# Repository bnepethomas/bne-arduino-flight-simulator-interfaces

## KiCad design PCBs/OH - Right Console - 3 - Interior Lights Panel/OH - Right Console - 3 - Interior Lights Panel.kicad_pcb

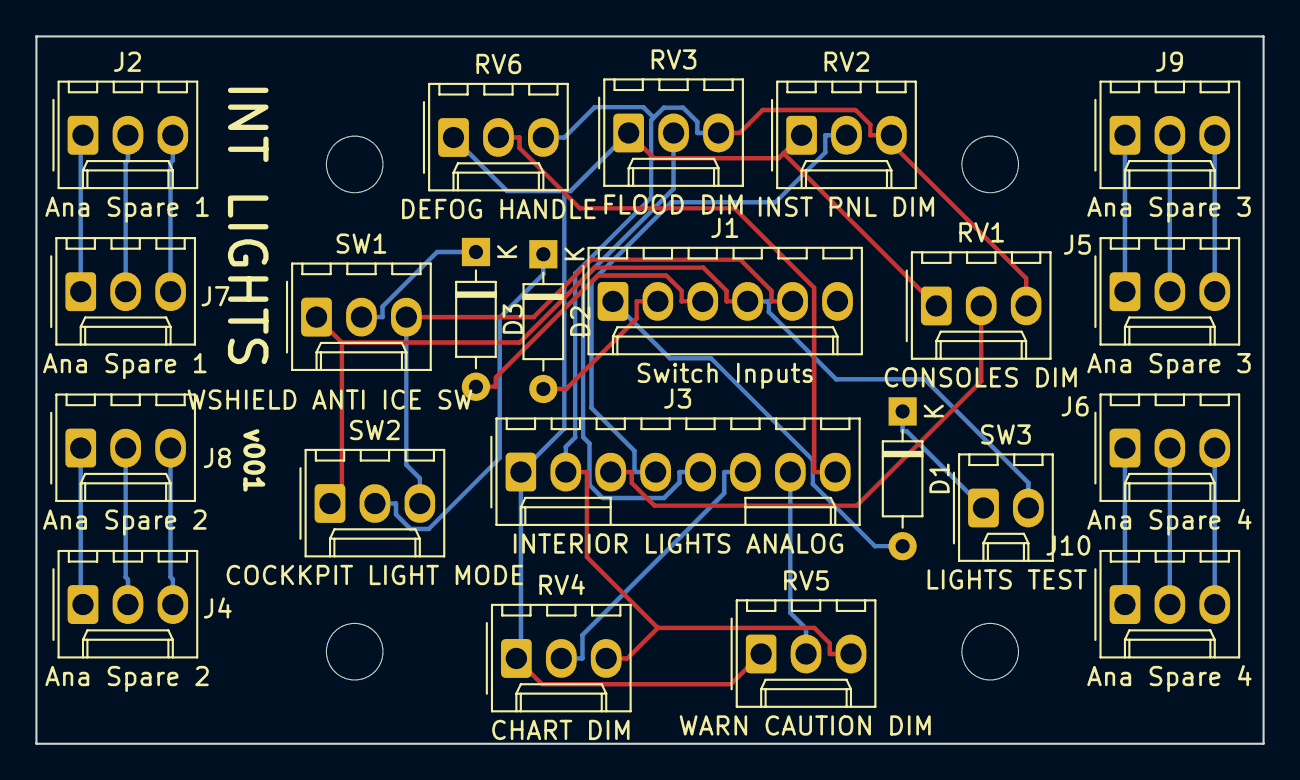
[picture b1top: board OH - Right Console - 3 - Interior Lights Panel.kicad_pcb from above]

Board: 2 copper layers, 69.4 x 40.0 mm, 26 parts (0 on the bottom side), 28 nets.

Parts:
D1, D2, D3: D; D_Signal_P7.62mm_Horizontal
H1, H2, H3, H4: MountingHole; MountingHole_3.2mm_M3
J1: Switch Inputs; Molex_1x06_P2.54mm_Vertical
J2, J7: Ana Spare 1; Molex_1x03_P2.54mm_Vertical
J3: INTERIOR LIGHTS ANALOG; Molex_1x08_P2.54mm_Vertical
J4, J8: Ana Spare 2; Molex_1x03_P2.54mm_Vertical
J5, J9: Ana Spare 3; Molex_1x03_P2.54mm_Vertical
J6, J10: Ana Spare 4; Molex_1x03_P2.54mm_Vertical
RV1: CONSOLES DIM; Molex_1x03_P2.54mm_Vertical
RV2: INST PNL DIM; Molex_1x03_P2.54mm_Vertical
RV3: FLOOD DIM; Molex_1x03_P2.54mm_Vertical
RV4: CHART DIM; Molex_1x03_P2.54mm_Vertical
RV5: WARN CAUTION DIM; Molex_1x03_P2.54mm_Vertical
RV6: DEFOG HANDLE; Molex_1x03_P2.54mm_Vertical
SW1: WSHIELD ANTI ICE SW; Molex_1x03_P2.54mm_Vertical
SW2: COCKKPIT LIGHT MODE; Molex_1x03_P2.54mm_Vertical
SW3: LIGHTS TEST; Molex_1x02_P2.54mm_Vertical

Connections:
/ANALOG+5V: J3.1, RV1.1, RV2.1, RV3.1, RV4.1, RV5.1, RV6.1
/ANALOG_GND: J3.2, RV1.3, RV2.3, RV3.3, RV4.3, RV5.3, RV6.3
/CHART: J3.6, RV4.2
/CONSOLES: J3.3, RV1.2
/Col1: D1.2, J1.1
/Col2: D2.2, J1.2
/Col3: D3.2, J1.3
/DEFOG: J3.8, RV6.2
/FLOOD: J3.5, RV3.2
/INST_PNL: J3.4, RV2.2
/ROW1: J1.4, SW1.1, SW2.1, SW3.2
/ROW2: J1.5, SW1.3, SW2.3
/WARN_CAUTION: J3.7, RV5.2
unnamed: D1.1, SW3.1
unnamed: D2.1, SW2.2
unnamed: D3.1, SW1.2
unnamed: J2.1, J7.1
unnamed: J2.2, J7.2
unnamed: J2.3, J7.3
unnamed: J4.1, J8.1
unnamed: J4.2, J8.2
unnamed: J4.3, J8.3
unnamed: J5.1, J9.1
unnamed: J5.2, J9.2
unnamed: J5.3, J9.3
unnamed: J6.1, J10.1
unnamed: J6.2, J10.2
unnamed: J6.3, J10.3

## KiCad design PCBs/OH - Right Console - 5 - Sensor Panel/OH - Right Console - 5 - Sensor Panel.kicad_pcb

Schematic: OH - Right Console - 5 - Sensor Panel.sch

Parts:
D1, D2, D3, D4, D5, D6: D; D_Signal_P7.62mm_Horizontal
D7: 1N4001; D_DO-41_SOD81_P10.16mm_Horizontal
H1, H2, H3, H4: MountingHole; MountingHole_3.2mm_M3
J1: Input Coulmns; Molex_1x03_P2.54mm_Vertical
J2: Laser Mag; Molex_1x02_P2.54mm_Vertical
J3: Input Rows; Molex_1x08_P2.54mm_Vertical
SOL1: Laser Mag; Molex_1x02_P2.54mm_Vertical
SW1: FLIR; Molex_1x03_P2.54mm_Vertical
SW2: LTD/R; Molex_1x02_P2.54mm_Vertical
SW3: LST/NFLR; Molex_1x02_P2.54mm_Vertical
SW4: RADAR PULL; Molex_1x02_P2.54mm_Vertical
SW5: RADAR; Molex_1x06_P2.54mm_Vertical
SW6: INS; Molex_1x10_P2.54mm_Vertical

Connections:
/Col2: D5.2 (A), J1.2
/Col3: D6.2 (A), J1.3
/Row1: J3.1, SW1.1, SW5.1, SW6.1
/Row2: J3.2, SW1.3, SW5.2, SW6.2
/Row3: J3.3, SW2.2 (B), SW5.3, SW6.3
/Row4: J3.4, SW3.2 (B), SW5.4, SW6.4
/Row5: J3.5, SW4.2, SW6.5
/Row6: J3.6, SW6.6
/Row7: J3.7, SW6.7
/Row8: J3.8, SW6.8
unnamed: D1.1 (K), SW1.2
unnamed: D1.2 (A), D2.2 (A), D3.2 (A), D4.2 (A), J1.1
unnamed: D2.1 (K), SW2.1 (A)
unnamed: D3.1 (K), SW3.1 (A)
unnamed: D4.1 (K), SW4.1
unnamed: D5.1 (K), SW5.6 (COM)
unnamed: D6.1 (K), SW6.10
unnamed: D7.1, J2.1, SOL1.1
unnamed: D7.2, J2.2, SOL1.2

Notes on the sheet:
-- 5. Sensor Panel define3PosTumb("FLIR_SW", 62, 3001, 439, "Sensor Panel", "FLIR Switch, ON/STBY/OFF") define3PosTumb("LTD_R_SW", 62, 3002, 441, "Sensor Panel", "LTD/R Switch, ---/SAFE/AFT") -- ARM position is handled by another parameter defineToggleSwitch("LST_NFLR_SW", 62, 3004, 442, "Sensor Pa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

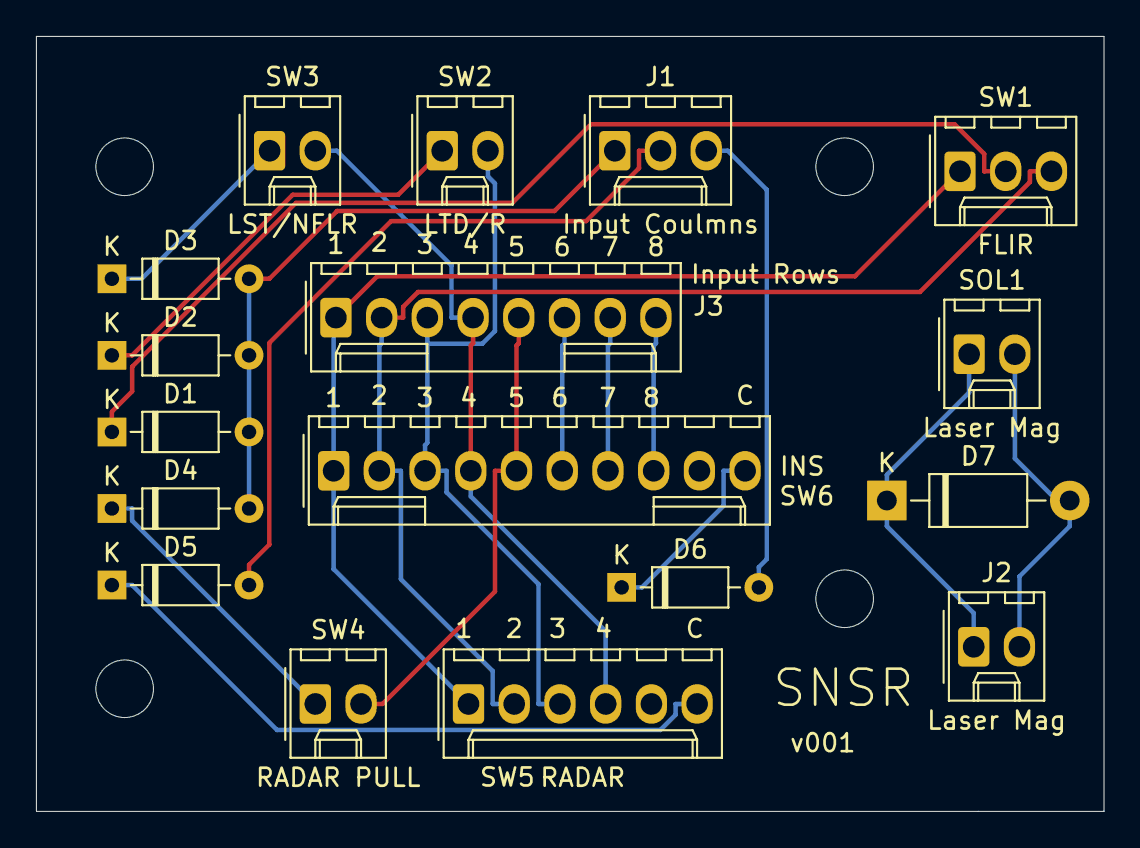
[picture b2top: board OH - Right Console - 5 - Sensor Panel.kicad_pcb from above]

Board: 2 copper layers, 59.3 x 43.1 mm, 21 parts (0 on the bottom side), 19 nets.

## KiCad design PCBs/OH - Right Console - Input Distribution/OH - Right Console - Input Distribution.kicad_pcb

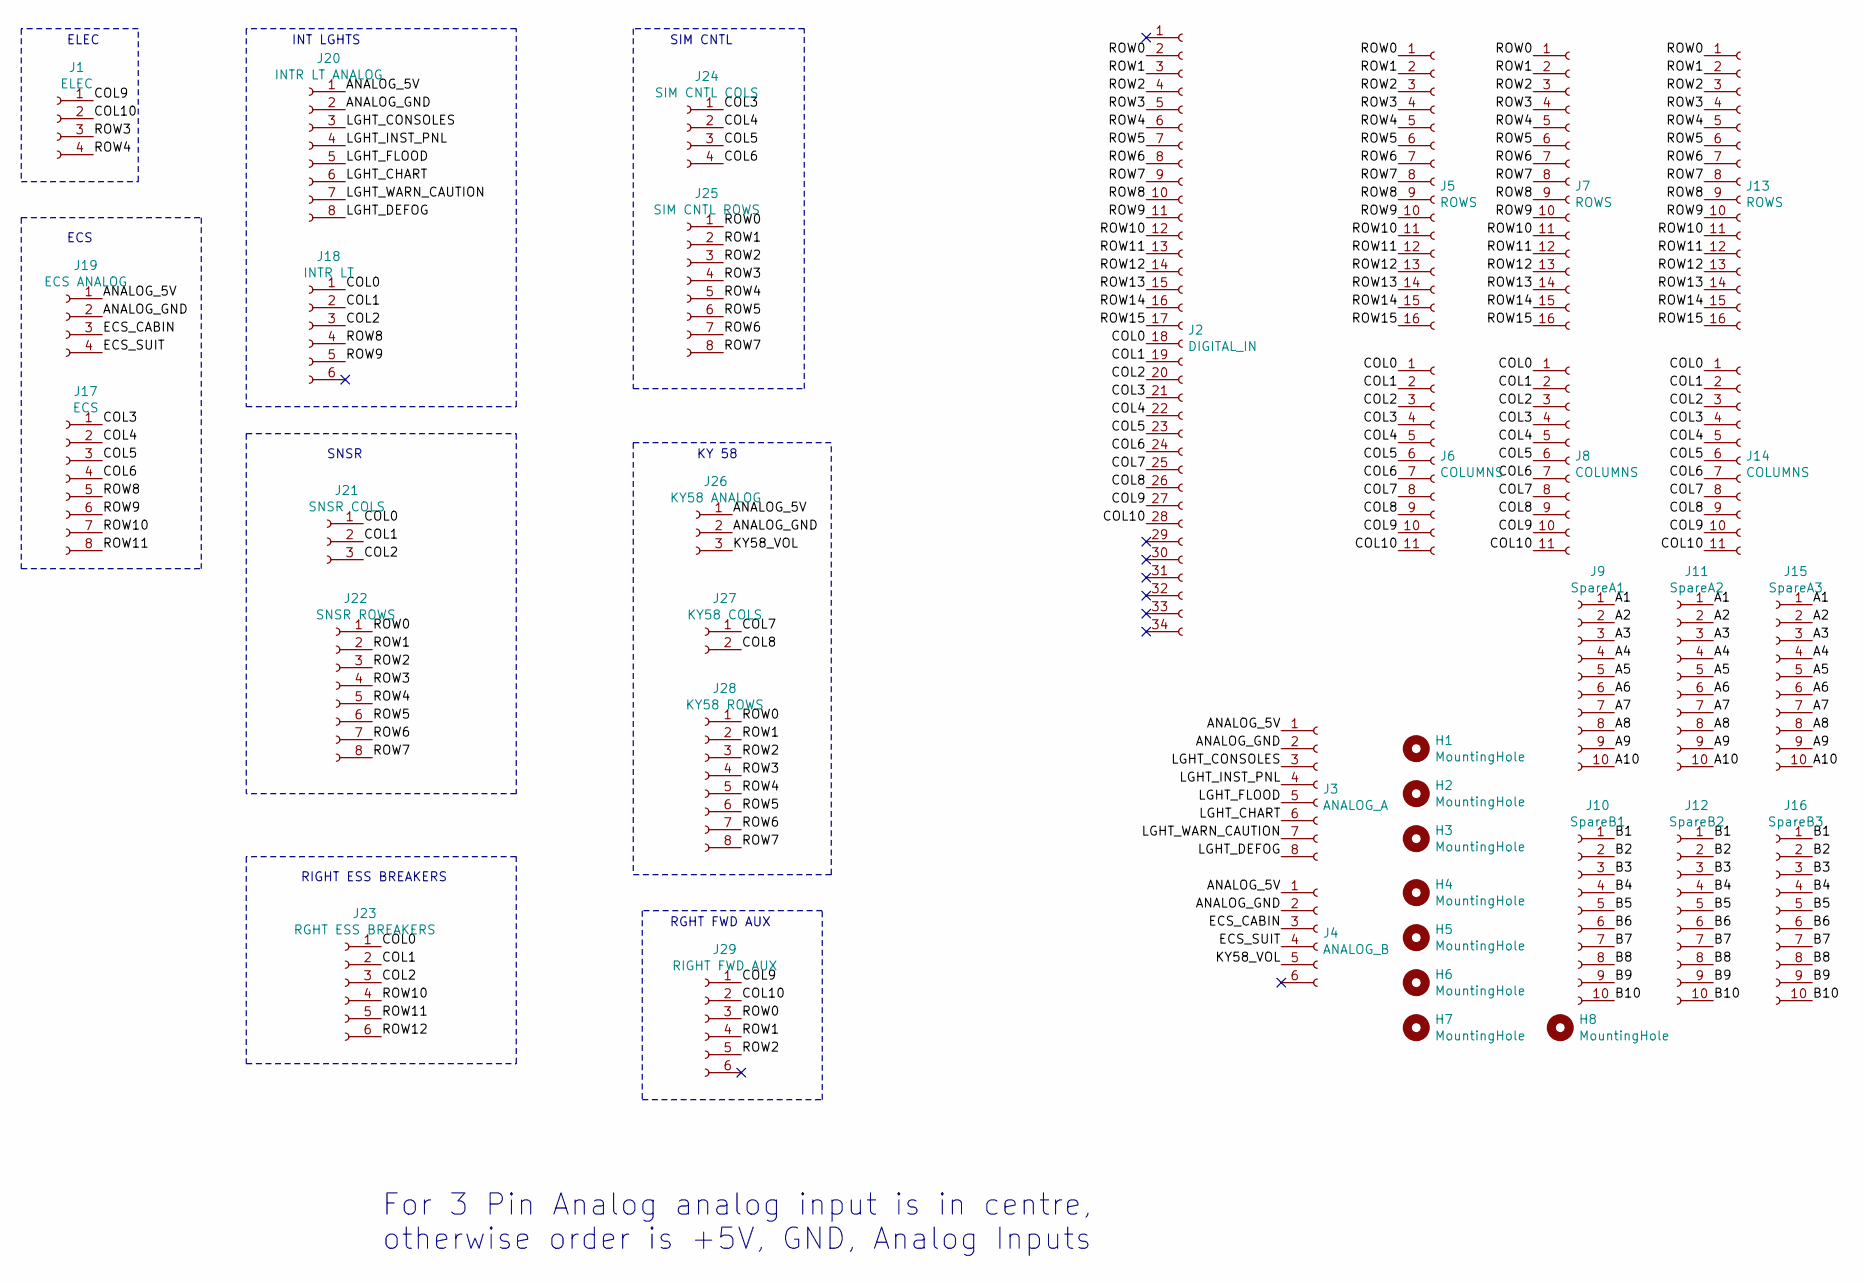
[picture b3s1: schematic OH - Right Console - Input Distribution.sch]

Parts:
H1, H2, H3, H4, H5, H6, H7, H8: MountingHole; MountingHole_3.2mm_M3
J1: ELEC; Molex_1x04_P2.54mm_Vertical
J2: DIGITAL_IN; IDC-Header_2x17_P2.54mm_Vertical
J3: ANALOG_A; Molex_1x08_P2.54mm_Vertical
J4: ANALOG_B; Molex_1x06_P2.54mm_Vertical
J5, J7, J13: ROWS; PinHeader_1x16_P2.54mm_Vertical
J6, J8, J14: COLUMNS; PinHeader_1x11_P2.54mm_Vertical
J9: SpareA1; Molex_1x10_P2.54mm_Vertical
J10: SpareB1; Molex_1x10_P2.54mm_Vertical
J11: SpareA2; Molex_1x10_P2.54mm_Vertical
J12: SpareB2; Molex_1x10_P2.54mm_Vertical
J15: SpareA3; Molex_1x10_P2.54mm_Vertical
J16: SpareB3; Molex_1x10_P2.54mm_Vertical
J17: ECS; Molex_1x08_P2.54mm_Vertical
J18: INTR LT; Molex_1x06_P2.54mm_Vertical
J19: ECS ANALOG; Molex_1x04_P2.54mm_Vertical
J20: INTR LT ANALOG; Molex_1x08_P2.54mm_Vertical
J21: SNSR COLS; Molex_1x03_P2.54mm_Vertical
J22: SNSR ROWS; Molex_1x08_P2.54mm_Vertical
J23: RGHT ESS BREAKERS; Molex_1x06_P2.54mm_Vertical
J24: SIM CNTL COLS; Molex_1x04_P2.54mm_Vertical
J25: SIM CNTL ROWS; Molex_1x08_P2.54mm_Vertical
J26: KY58 ANALOG; Molex_1x03_P2.54mm_Vertical
J27: KY58 COLS; Molex_1x02_P2.54mm_Vertical
J28: KY58 ROWS; Molex_1x08_P2.54mm_Vertical
J29: RIGHT FWD AUX; Molex_1x06_P2.54mm_Vertical

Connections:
/A1: J9.1, J11.1, J15.1
/A2: J9.2, J11.2, J15.2
/A3: J9.3, J11.3, J15.3
/A4: J9.4, J11.4, J15.4
/A5: J9.5, J11.5, J15.5
/A6: J9.6, J11.6, J15.6
/A7: J9.7, J11.7, J15.7
/A8: J9.8, J11.8, J15.8
/A9: J9.9, J11.9, J15.9
/A10: J9.10, J11.10, J15.10
/ANALOG_5V: J3.1, J4.1, J19.1, J20.1, J26.1
/ANALOG_GND: J3.2, J4.2, J19.2, J20.2, J26.2
/B1: J10.1, J12.1, J16.1
/B2: J10.2, J12.2, J16.2
/B3: J10.3, J12.3, J16.3
/B4: J10.4, J12.4, J16.4
/B5: J10.5, J12.5, J16.5
/B6: J10.6, J12.6, J16.6
/B7: J10.7, J12.7, J16.7
/B8: J10.8, J12.8, J16.8
/B9: J10.9, J12.9, J16.9
/B10: J10.10, J12.10, J16.10
/COL0: J2.18, J6.1, J8.1, J14.1, J18.1, J21.1, J23.1
/COL1: J2.19, J6.2, J8.2, J14.2, J18.2, J21.2, J23.2
/COL2: J2.20, J6.3, J8.3, J14.3, J18.3, J21.3, J23.3
/COL3: J2.21, J6.4, J8.4, J14.4, J17.1, J24.1
/COL4: J2.22, J6.5, J8.5, J14.5, J17.2, J24.2
/COL5: J2.23, J6.6, J8.6, J14.6, J17.3, J24.3
/COL6: J2.24, J6.7, J8.7, J14.7, J17.4, J24.4
/COL7: J2.25, J6.8, J8.8, J14.8, J27.1
/COL8: J2.26, J6.9, J8.9, J14.9, J27.2
/COL9: J1.1, J2.27, J6.10, J8.10, J14.10, J29.1
/COL10: J1.2, J2.28, J6.11, J8.11, J14.11, J29.2
/ECS_CABIN: J4.3, J19.3
/ECS_SUIT: J4.4, J19.4
/KY58_VOL: J4.5, J26.3
/LGHT_CHART: J3.6, J20.6
/LGHT_CONSOLES: J3.3, J20.3
/LGHT_DEFOG: J3.8, J20.8
/LGHT_FLOOD: J3.5, J20.5
/LGHT_INST_PNL: J3.4, J20.4
/LGHT_WARN_CAUTION: J3.7, J20.7
/ROW0: J2.2, J5.1, J7.1, J13.1, J22.1, J25.1, J28.1, J29.3
/ROW1: J2.3, J5.2, J7.2, J13.2, J22.2, J25.2, J28.2, J29.4
/ROW2: J2.4, J5.3, J7.3, J13.3, J22.3, J25.3, J28.3, J29.5
/ROW3: J1.3, J2.5, J5.4, J7.4, J13.4, J22.4, J25.4, J28.4
/ROW4: J1.4, J2.6, J5.5, J7.5, J13.5, J22.5, J25.5, J28.5
/ROW5: J2.7, J5.6, J7.6, J13.6, J22.6, J25.6, J28.6
/ROW6: J2.8, J5.7, J7.7, J13.7, J22.7, J25.7, J28.7
/ROW7: J2.9, J5.8, J7.8, J13.8, J22.8, J25.8, J28.8
/ROW8: J2.10, J5.9, J7.9, J13.9, J17.5, J18.4
/ROW9: J2.11, J5.10, J7.10, J13.10, J17.6, J18.5
/ROW10: J2.12, J5.11, J7.11, J13.11, J17.7, J23.4
/ROW11: J2.13, J5.12, J7.12, J13.12, J17.8, J23.5
/ROW12: J2.14, J5.13, J7.13, J13.13, J23.6
/ROW13: J2.15, J5.14, J7.14, J13.14
/ROW14: J2.16, J5.15, J7.15, J13.15
/ROW15: J2.17, J5.16, J7.16, J13.16

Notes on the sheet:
ELEC
For 3 Pin Analog analog input is in centre, otherwise order is +5V, GND, Analog Inputs
ECS
INT LGHTS
SNSR
RIGHT ESS BREAKERS
SIM CNTL
KY 58
RGHT FWD AUX

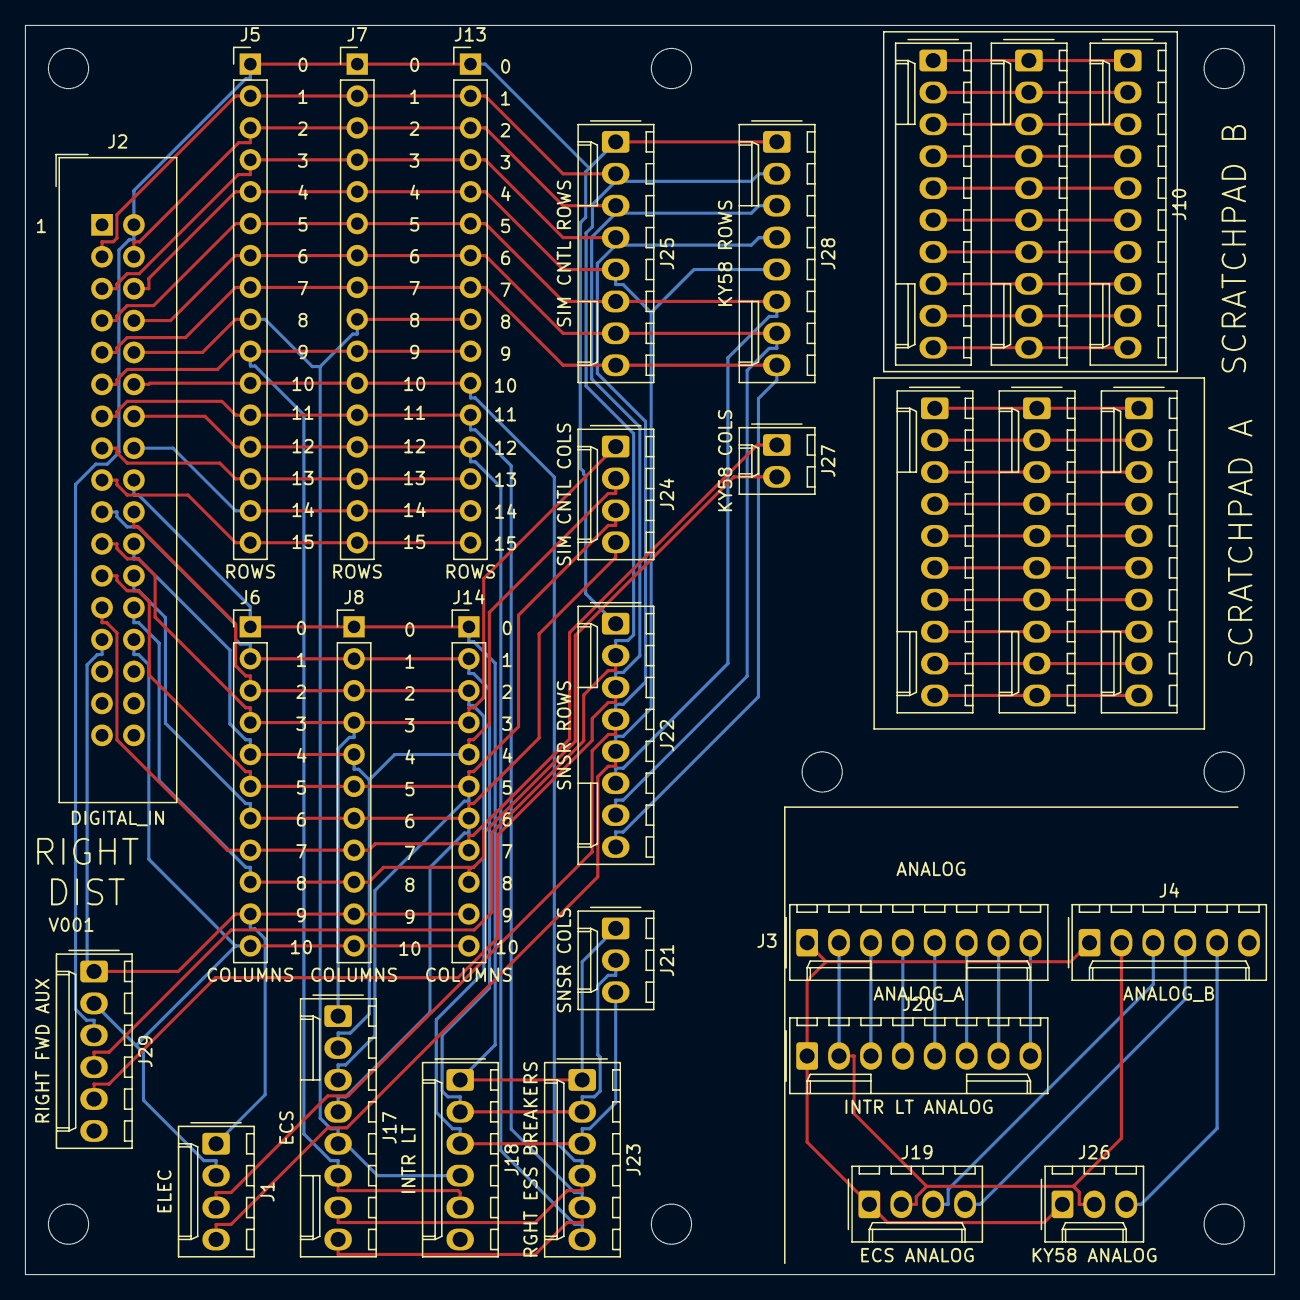
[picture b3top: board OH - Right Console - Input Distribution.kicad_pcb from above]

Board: 2 copper layers, 99.4 x 99.4 mm, 37 parts (0 on the bottom side), 58 nets.

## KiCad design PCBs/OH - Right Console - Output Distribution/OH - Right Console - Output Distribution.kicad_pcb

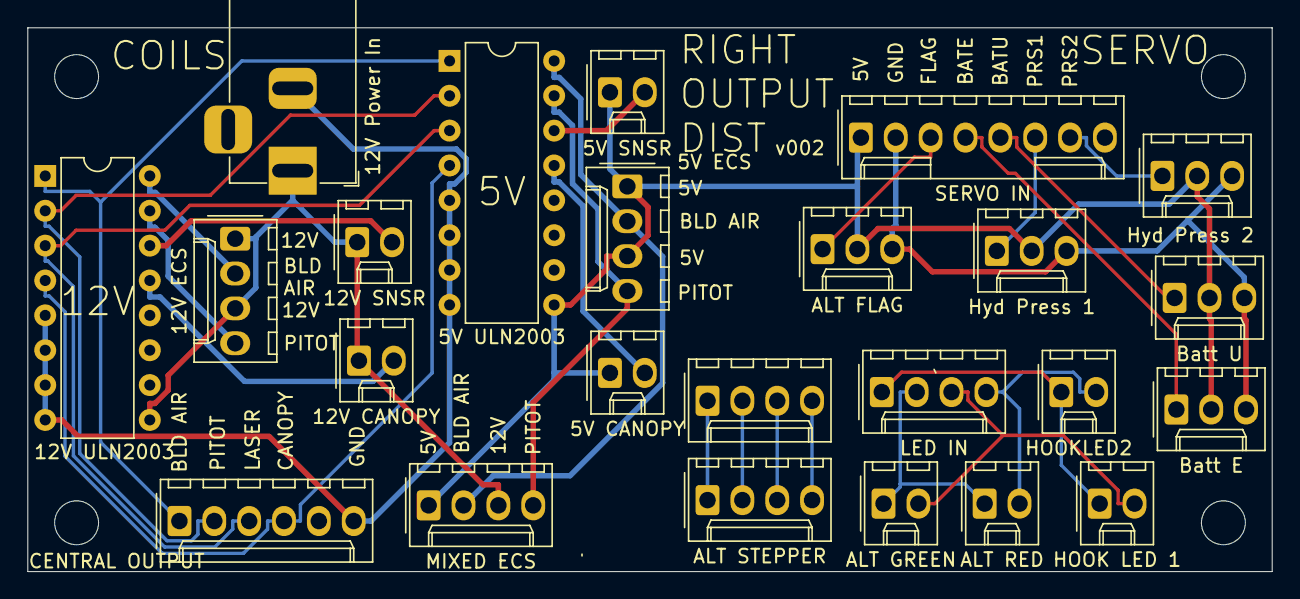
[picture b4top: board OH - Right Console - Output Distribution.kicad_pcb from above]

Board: 2 copper layers, 90.7 x 39.6 mm, 28 parts (0 on the bottom side), 29 nets.

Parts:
H1, H2, H3, H4: MountingHole; MountingHole_3.2mm_M3
J1: CENTRAL OUTPUT; Molex_1x06_P2.54mm_Vertical
J2: SERVO IN; Molex_1x08_P2.54mm_Vertical
J3: 12V Power In; BarrelJack_Horizontal
J4, J7: ALT STEPPER; Molex_1x04_P2.54mm_Vertical
J5: 5V ECS; Molex_1x04_P2.54mm_Vertical
J6: LED IN; Molex_1x04_P2.54mm_Vertical
J8: ALT FLAG; Molex_1x03_P2.54mm_Vertical
J9: HOOK LED 1; Molex_1x02_P2.54mm_Vertical
J10: ALT GREEN; Molex_1x02_P2.54mm_Vertical
J11: HOOKLED2; Molex_1x02_P2.54mm_Vertical
J12: ALT RED; Molex_1x02_P2.54mm_Vertical
J13: 12V ECS; Molex_1x04_P2.54mm_Vertical
J14: 12V SNSR; Molex_1x02_P2.54mm_Vertical
J15: 12V CANOPY; Molex_1x02_P2.54mm_Vertical
J16: Batt U; Molex_1x03_P2.54mm_Vertical
J17: Batt E; Molex_1x03_P2.54mm_Vertical
J18: Hyd Press 1; Molex_1x03_P2.54mm_Vertical
J19: Hyd Press 2; Molex_1x03_P2.54mm_Vertical
J20: 5V SNSR; Molex_1x02_P2.54mm_Vertical
J21: 5V CANOPY; Molex_1x02_P2.54mm_Vertical
J22: MIXED ECS; Molex_1x04_P2.54mm_Vertical
U1: 12V ULN2003; DIP-16_W7.62mm
U2: 5V ULN2003; DIP-16_W7.62mm

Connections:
/5V_Out_Bleed_Air_Sol: J5.2, J22.2, U2.16
/5V_Out_Canopy_Mag: J21.2, U2.13
/5V_Out_Laser_Arm_Mag: J20.2, U2.14
/5V_Out_Pitot_Heat_Mag: J5.4, J22.4, U2.15
/12V_Out_Bleed_Air_Sol: J13.2, U1.16
/12V_Out_Canopy_Mag: J15.2, U1.13
/12V_Out_Laser_Arm_Mag: J14.2, U1.14
/12V_Out_Pitot_Heat_Mag: J13.4, U1.15
/+12V: J3.1, J13.1, J13.3, J14.1, J15.1, J22.3, U1.9
/ALT_FLAG_PWM: J2.3, J8.1
/ALT_STEPPER_1A: J4.1, J7.1
/ALT_STEPPER_1B: J4.2, J7.2
/ALT_STEPPER_2A: J4.3, J7.3
/ALT_STEPPER_2B: J4.4, J7.4
/BATT_E_PWM: J2.4, J17.1
/BATT_U_PWM: J2.5, J16.1
/GND: J1.6, J3.2, U1.5, U1.6, U1.7, U1.8, U2.5, U2.6, U2.7, U2.8
/HYD_PRESS_1_PWM: J2.6, J18.1
/HYD_PRESS_2_PWM: J2.7, J19.1
/In_Bleed_Air_Sol: J1.1, U1.1, U2.1
/In_Canopy_Mag: J1.4, U1.4, U2.4
/In_Laser_Arm_Mag: J1.3, U1.3, U2.3
/In_Pitot_Heat_Mag: J1.2, U1.2, U2.2
/LEDCOL1: J6.3, J9.2, J10.2
/LEDCOL2: J6.4, J11.2, J12.2
/LEDROW1: J6.1, J9.1, J11.1
/LEDROW2: J6.2, J10.1, J12.1
/SERVO_5V: J2.1, J5.1, J5.3, J8.2, J16.2, J17.2, J18.2, J19.2, J20.1, J21.1, J22.1, U2.9
/SERVO_GND: J2.2, J8.3, J16.3, J17.3, J18.3, J19.3

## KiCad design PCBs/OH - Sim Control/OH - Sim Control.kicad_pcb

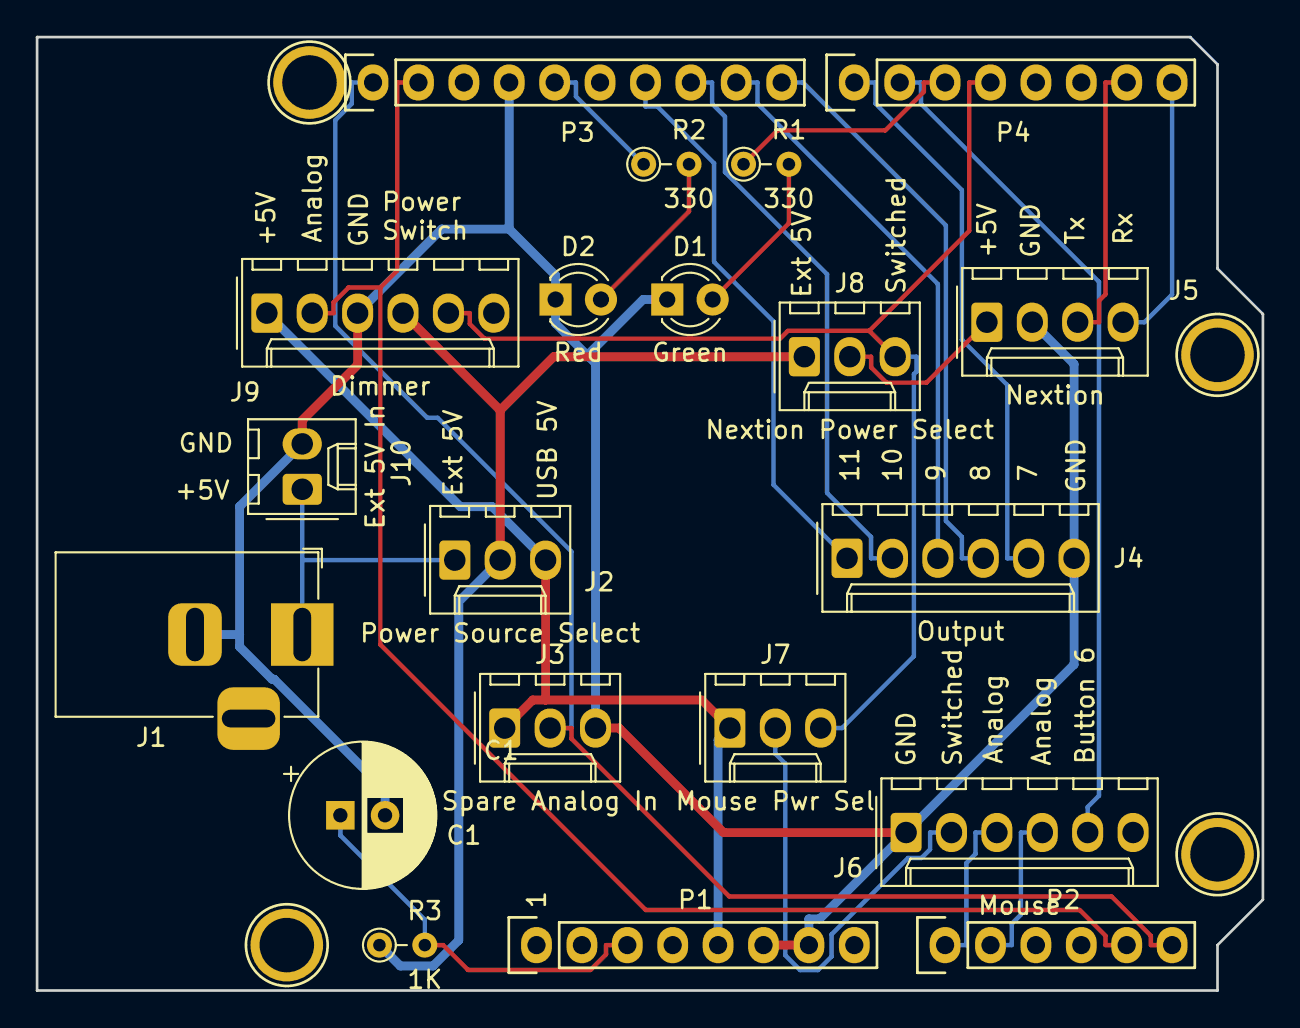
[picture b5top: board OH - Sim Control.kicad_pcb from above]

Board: 2 copper layers, 68.6 x 53.3 mm, 24 parts (0 on the bottom side), 24 nets.

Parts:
C1: CP; PT_CP_Radial_D8.0mm_P2.50mm
D1: Green; LED_D3.0mm
D2: Red; LED_D3.0mm
J1: Ext 5V In; BarrelJack_Horizontal
J2: Power Source Select; Molex_1x03_P2.54mm_Vertical
J3: Spare Analog In; Molex_1x03_P2.54mm_Vertical
J4: Output; Molex_1x06_P2.54mm_Vertical
J5: Nextion; Molex_1x04_P2.54mm_Vertical
J6: Mouse; Molex_1x06_P2.54mm_Vertical
J7: Mouse Pwr Sel; Molex_1x03_P2.54mm_Vertical
J8: Nextion Power Select; Molex_1x03_P2.54mm_Vertical
J9: Dimmer; Molex_1x06_P2.54mm_Vertical
J10: Ext 5V In; Molex_1x02_P2.54mm_Vertical
P1: Power; Socket_Strip_Arduino_1x08
P2: Analog; Socket_Strip_Arduino_1x06
P3: Digital; Socket_Strip_Arduino_1x10
P4: Digital; Socket_Strip_Arduino_1x08
P5, P6, P7, P8: CONN_01X01; Arduino_1pin
R1, R2: 330; PT_R_Axial_DIN0204_L3.6mm_D1.6mm_P2.54mm_Vertical
R3: 1K; PT_R_Axial_DIN0204_L3.6mm_D1.6mm_P2.54mm_Vertical

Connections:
+5V: J2.3, J3.1, J7.1, J9.1, P1.5
+5VD: J2.2, J8.1, J9.4, R3.1
/0(Rx): J5.4, P4.8
/1(Tx): J5.3, P4.7
/5(**): P4.3, R1.1
/6: J6.5, P4.2
/7: J4.5, P4.1
/8: J4.4, P3.10
/9: J4.3, P3.9
/10: J4.2, P3.8
/11: J4.1, P3.7
/13(SCK): P3.5, R2.1
/A0: J6.3, P2.1
/A1: J6.4, P2.2
/A4(SDA): J9.2, P2.5, P3.2
/A5(SCL): J3.2, P2.6, P3.1
/Reset: C1.1, P1.3, R3.2
/Swtiched_5VD: J7.3, J8.3, J9.5, P4.4
GND: C1.2, D1.1, D2.1, J1.2, J3.3, J4.6, J5.2, J6.1, J9.3, J10.2, P1.6, P1.7, P3.4
unnamed: D1.2, R1.2
unnamed: D2.2, R2.2
unnamed: J1.1, J2.1, J10.1
unnamed: J5.1, J8.2
unnamed: J6.2, J7.2

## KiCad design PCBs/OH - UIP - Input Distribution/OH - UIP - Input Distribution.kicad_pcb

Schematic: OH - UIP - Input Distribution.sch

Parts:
D1, D2, D3, D4: D; D_Signal_P7.62mm_Horizontal
H1, H2, H3, H4, H5, H6, H7, H8: MountingHole; MountingHole_3.2mm_M3
J1: JET STATION SEL; Molex_1x06_P2.54mm_Vertical
J2: AP COL; Molex_1x03_P2.54mm_Vertical
J3: LEFT DDI COL; Molex_1x06_P2.54mm_Vertical
J4: LEFT DDI ROW; Molex_1x06_P2.54mm_Vertical
J5: RIGHT DDI COL; Molex_1x06_P2.54mm_Vertical
J6: RIGHT DDI ROW; Molex_1x06_P2.54mm_Vertical
J7: UFC COL; Molex_1x04_P2.54mm_Vertical
J8: UFC ROW; Molex_1x06_P2.54mm_Vertical
J9: AMPCD COL; Molex_1x04_P2.54mm_Vertical
J10: AMPCD ROW; Molex_1x08_P2.54mm_Vertical
J11: RWR CONTROL; Molex_1x08_P2.54mm_Vertical
J12: IFEI; Molex_1x08_P2.54mm_Vertical
J13: BIT; Molex_1x02_P2.54mm_Vertical
J14: MASTER ARM; Molex_1x06_P2.54mm_Vertical
J15: HUD CONTROL; Molex_1x06_P2.54mm_Vertical
J16: ECM; Molex_1x08_P2.54mm_Vertical
J17: SPIN; Molex_1x04_P2.54mm_Vertical
J18: LEFT EWI COL; Molex_1x02_P2.54mm_Vertical
J19: LEFT EWI ROW; Molex_1x02_P2.54mm_Vertical
J20: REWICOL; Molex_1x02_P2.54mm_Vertical
J21: REWIROW; Molex_1x02_P2.54mm_Vertical
J22: IFEI BRIGHTNESS; Molex_1x03_P2.54mm_Vertical
J23: SPIN ANALOG; Molex_1x03_P2.54mm_Vertical
J24: STANDBY ANALOG; Molex_1x03_P2.54mm_Vertical
J25: LEFT DDI ANALOG; Molex_1x04_P2.54mm_Vertical
J26: AMPCD-HDG; Molex_1x03_P2.54mm_Vertical
J27: ENCODERS; Molex_1x10_P2.54mm_Vertical
J28: HUD ANALOG; Molex_1x06_P2.54mm_Vertical
J29: RWR ANALOG; Molex_1x04_P2.54mm_Vertical
J30: RIGHT DDI ANALOG; Molex_1x04_P2.54mm_Vertical
J31: ANALOG B; Molex_1x10_P2.54mm_Vertical
J32: ANALOG A; Molex_1x08_P2.54mm_Vertical
J33: AMPCD-CRS; Molex_1x03_P2.54mm_Vertical
J34: STANDBY ENCODERS; Molex_1x06_P2.54mm_Vertical
J35: UFC LEFT ENCODER; Molex_1x06_P2.54mm_Vertical
J36: UFC RIGHT ENCODER; Molex_1x06_P2.54mm_Vertical
J37: AMPCD-BRIGHT; Molex_1x03_P2.54mm_Vertical
J38: DIGITAL_IN; IDC-Header_2x17_P2.54mm_Vertical
J39: ROWS; PinHeader_1x16_P2.54mm_Vertical
J40: COLUMNS; PinHeader_1x11_P2.54mm_Vertical
J41: AP ROW; Molex_1x03_P2.54mm_Vertical

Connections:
/AMPCD-BRIGHTNESS: J31.10, J37.2
/ANALOG_5V: J22.1, J23.1, J24.1, J25.1, J28.1, J29.1, J30.1, J31.1, J32.1, J37.1
/ANALOG_GND: J22.3, J23.3, J24.3, J25.2, J28.2, J29.2, J30.2, J31.2, J32.2, J37.3
/BLK-LVL: J28.5, J32.5
/COL0: J3.1, J9.1, J12.1, J38.18, J40.1
/COL1: J3.2, J9.2, J12.2, J38.19, J40.2
/COL2: J3.3, J9.3, J12.3, J33.1, J38.20, J40.3
/COL3: J3.4, J9.4, J12.4, J33.3, J38.21, J40.4
/COL4: D3.2, D4.2, J3.5, J7.1, J11.1, J38.22, J40.5
/COL5: J5.1, J7.2, J11.2, J13.1, J38.23, J40.6
/COL6: J1.1, J5.2, J7.3, J14.1, J17.1, J38.24, J40.7
/COL7: J1.2, J5.3, J7.4, J14.2, J17.2, J38.25, J40.8
/COL8: J1.3, J2.1, J5.4, J15.1, J16.1, J38.26, J40.9
/COL9: J1.4, J2.2, J5.5, J15.2, J16.2, J18.1, J20.1, J38.27, J40.10
/COL10: D1.2, J1.5, J2.3, J15.3, J16.3, J18.2, J20.2, J38.28, J40.11
/ENCODER-GND: J27.1, J34.2, J34.5, J35.2, J36.2
/HUD-AOA: J28.4, J32.4
/HUD-BAL: J28.6, J32.6
/HUD-BRT: J28.3, J32.3
/IFEI-BRIGHTNESS: J22.2, J31.4
/LEFT-DDI-BRIGHT: J25.3, J31.6
/LEFT-DDI-CONT: J25.4, J31.7
/RIGHT-DDI-BRIGHT: J30.3, J31.8
/RIGHT-DDI-CONT: J30.4, J31.9
/ROW0: J4.1, J6.1, J26.1, J38.2, J39.1
/ROW1: J4.2, J6.2, J26.3, J38.3, J39.2
/ROW2: J4.3, J6.3, J38.4, J39.3, J41.1
/ROW3: J4.4, J6.4, J19.1, J35.6, J38.5, J39.4
/ROW4: J4.5, J6.5, J21.1, J36.6, J38.6, J39.5
/ROW5: J8.1, J10.1, J38.7, J39.6, J41.2
/ROW6: J8.2, J10.2, J38.8, J39.7, J41.3
/ROW7: J8.3, J10.3, J16.4, J38.9, J39.8
/ROW8: J8.4, J10.4, J16.5, J38.10, J39.9
/ROW9: J8.5, J10.5, J16.6, J38.11, J39.10
/ROW10: J8.6, J10.6, J13.2, J14.3, J16.7, J38.12, J39.11
/ROW11: J10.7, J11.3, J14.4, J16.8, J38.13, J39.12
/ROW12: J10.8, J11.4, J14.5, J15.4, J38.14, J39.13
/ROW13: J11.5, J12.5, J15.5, J17.3, J38.15, J39.14
/ROW14: J11.6, J12.6, J15.6, J17.4, J38.16, J39.15
/ROW15: D2.1, J1.6, J11.7, J12.7, J38.17, J39.16
/RWR-AUDIO: J29.3, J32.7
/RWR-DIMMER: J29.4, J32.8
/SPIN-ANALOG: J23.2, J31.3
/STANDBY-ANALOG: J24.2, J31.5
/STDBY-ENC-1-A: J27.2, J34.1
/STDBY-ENC-1-B: J27.3, J34.3
/STDBY-ENC-2-A: J27.4, J34.4
/STDBY-ENC-2-B: J27.5, J34.6
/UFC-LEFT-ENCODER-A: J27.6, J35.1
/UFC-LEFT-ENCODER-B: J27.7, J35.3
/UFC-RIGHT-ENCODER-A: J27.8, J36.1
/UFC-RIGHT-ENCODER-B: J27.9, J36.3
unnamed: D1.1, J26.2
unnamed: D2.2, J33.2
unnamed: D3.1, J35.5
unnamed: D4.1, J36.5

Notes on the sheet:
For 3 Pin Analog analog input is in centre, otherwise order is +5V, GND, Analog Inputs
LEFT DDI
RIGHT DDI
UFC
LEFT UFC PRESS
RIGHT UFC PRESS
NEED 8 I/O PINS FOR ENCODERS CAN’T USE 0/1 OR 13 BEST TO USE TOP LAYER IF POSSIBLE ON SHIELD

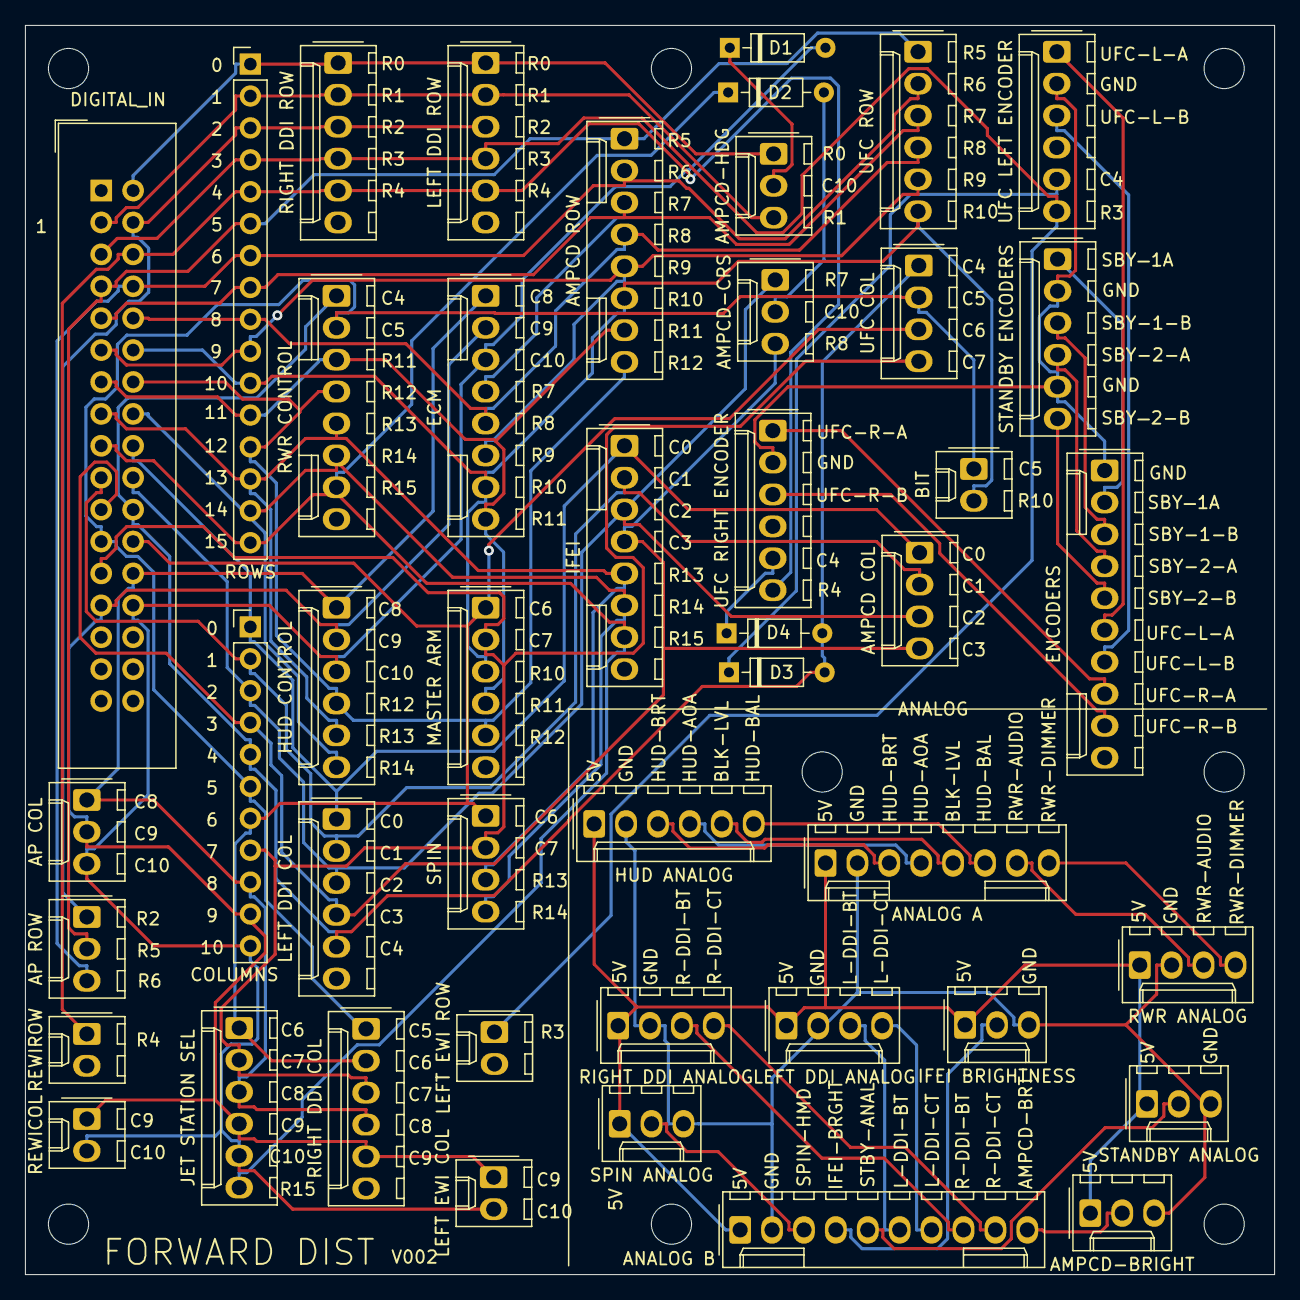
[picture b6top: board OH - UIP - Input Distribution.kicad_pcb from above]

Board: 2 copper layers, 99.4 x 99.4 mm, 53 parts (0 on the bottom side), 56 nets.
